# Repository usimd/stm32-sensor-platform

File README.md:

# stm32-sensor-platform
Extensible BLE/OpenThread sensor module based on STM32 for integration with HomeAssistant

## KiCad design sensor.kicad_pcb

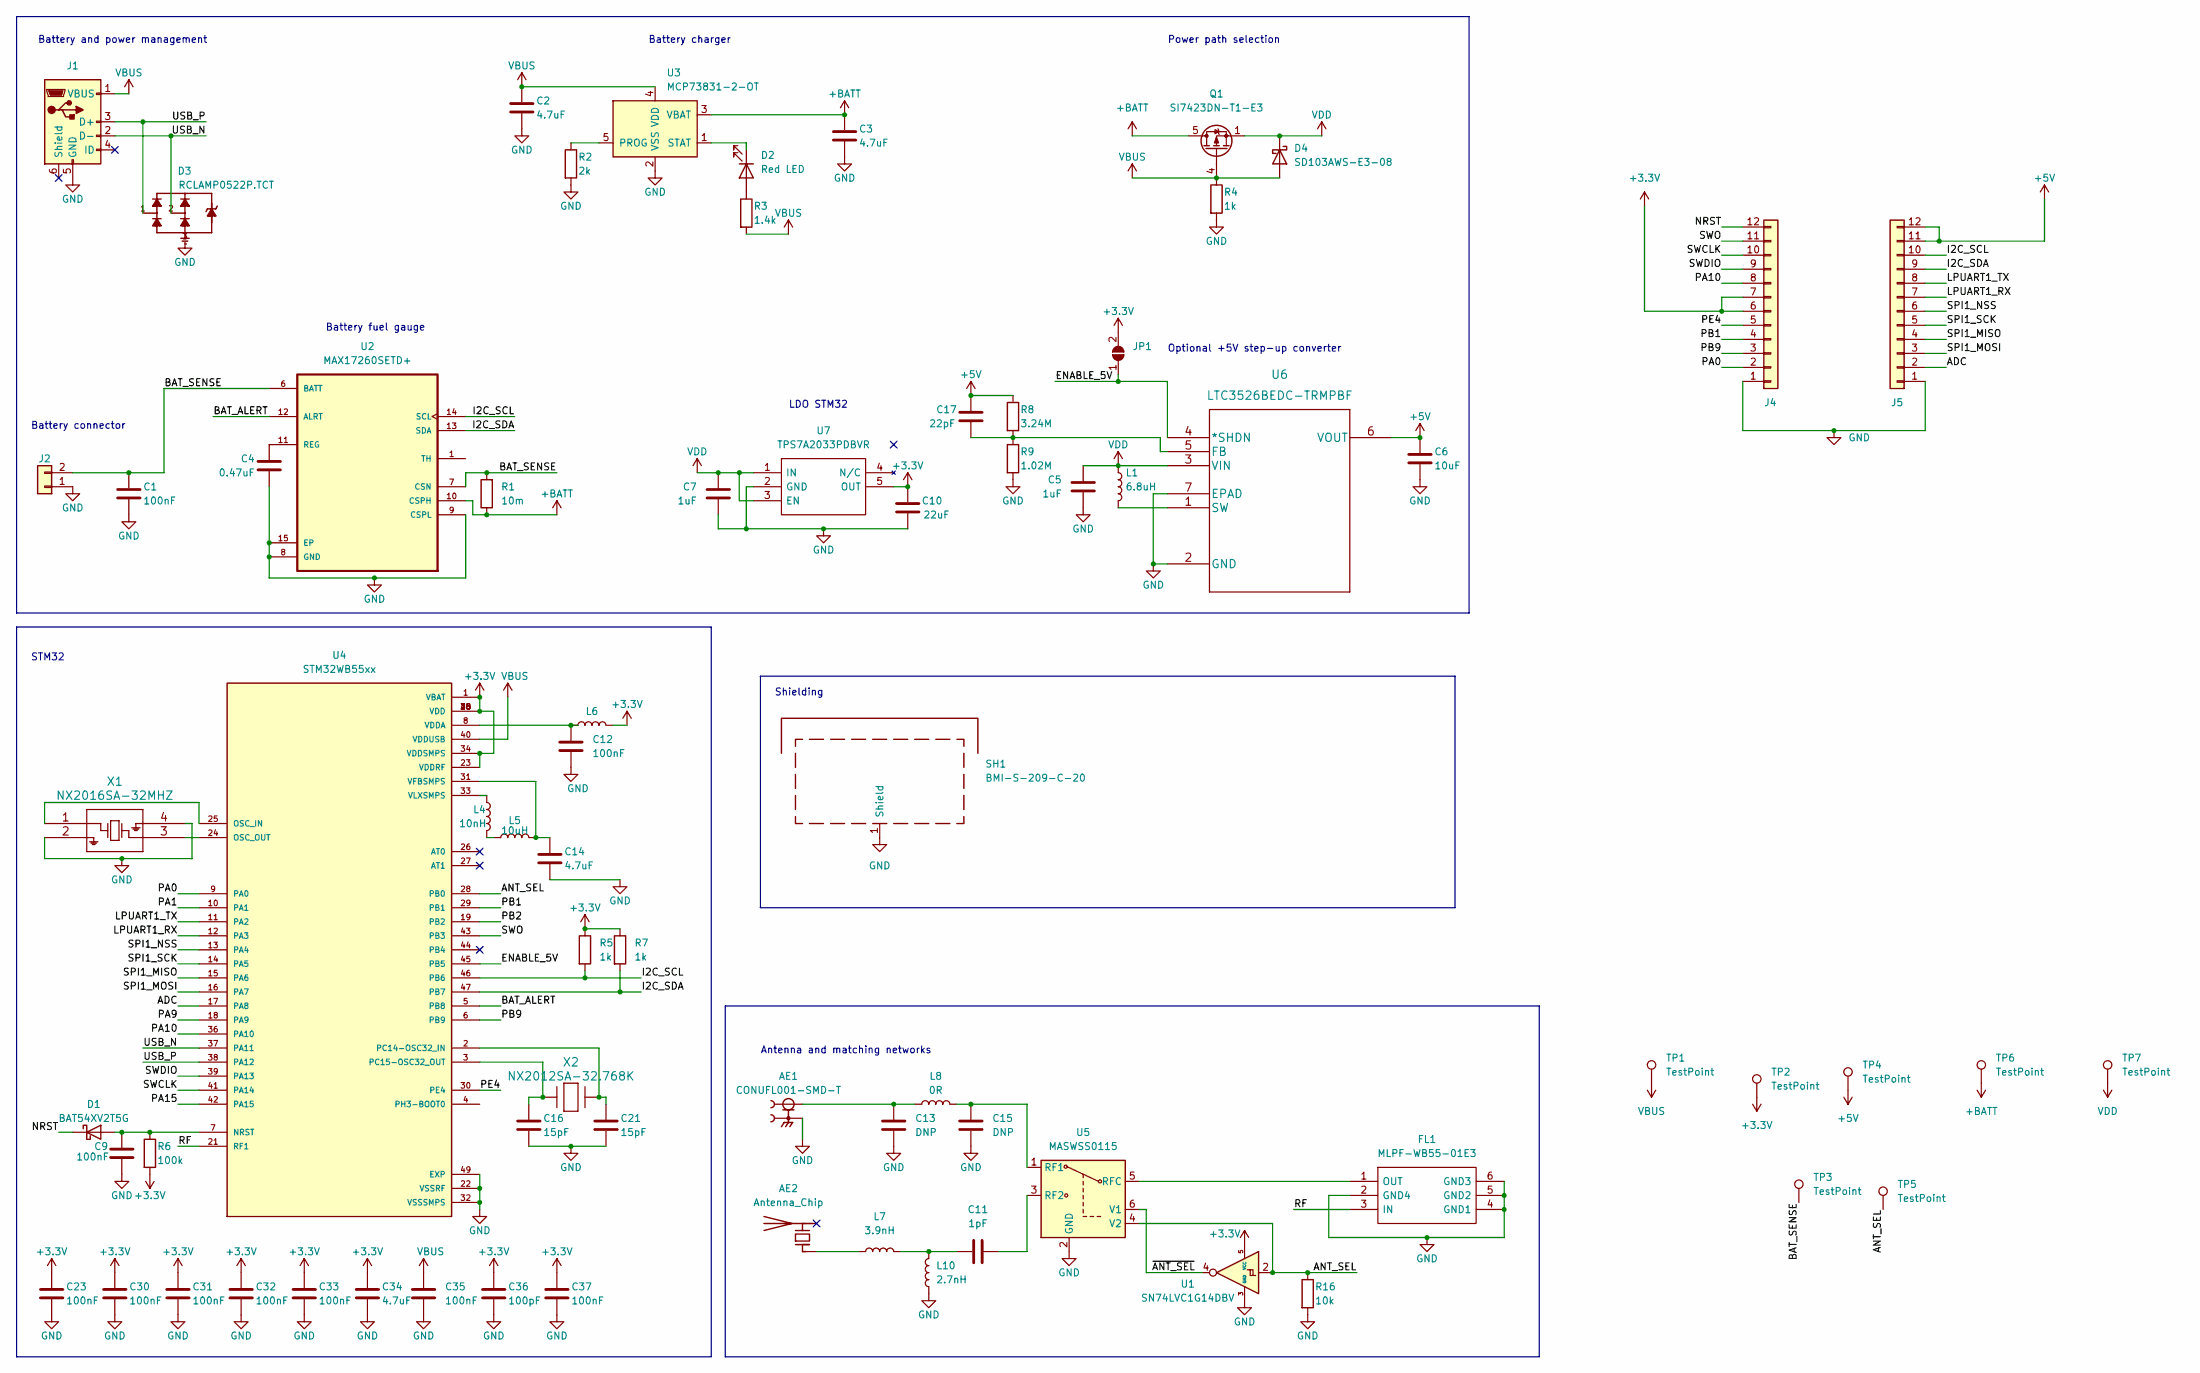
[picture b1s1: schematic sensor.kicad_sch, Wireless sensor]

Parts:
AE1: CONUFL001-SMD-T; LINX_CONUFL001-SMD-T; PARTREV B
AE2: Antenna_Chip; Johanson_2450AT18x100; MPN 2450AT18A100E
C1: 100nF; C_0402_1005Metric; MPN GRM155R62A104KE14J
C2, C3, C14, C34: 4.7uF; C_0402_1005Metric; MPN GRM155R61A475MEAAD
C4: 0.47uF; C_0603_1608Metric; MPN LMK063BBJ474KPLF
C5, C7: 1uF; C_0402_1005Metric; MPN CL05A105KP5NNNC
C6: 10uF; C_0603_1608Metric; MPN 0603ZD106KAT2A
C9, C12, C23, C30, C31, C32, C33, C35, C37: 100nF; C_0402_1005Metric; MPN GRM155R61H104KE19D
C10: 22uF; C_0603_1608Metric; MPN CL10A226KQ8NRNE
C11: 1pF; C_0402_1005Metric; MPN 500R07S1R0BV4T
C13, C15: DNP; C_0402_1005Metric
C16, C21: 15pF; C_0402_1005Metric; MPN GRM1555C1H4R3CA01D
C17: 22pF; C_0402_1005Metric; MPN C0402C220K4RACTU
C36: 100pF; C_0402_1005Metric; MPN CC0402KRX7R9BB101
D1: BAT54XV2T5G; D_SOD-523; MPN BAT54XV2T5G
D2: Red LED; LED_0603_1608Metric; MPN LS L29K-G1J2-1
D3: RCLAMP0522P.TCT; TVS_RCLAMP0522P.TCT; MPN RCLAMP0522P.TCT
D4: SD103AWS-E3-08; D_SOD-323; MPN SD103AWS-E3-08
FL1: MLPF-WB55-01E3; MLPFWB5501E3; Manufacturer_Part_Number MLPF-WB55-01E3; Mouser Part Number 511-MLPF-WB55-01E3
J1: 10103594-0001LF; USB_Micro-B_Amphenol_10103594-0001LF_Horizontal; MPN 10103594-0001LF
J2: Molex_PicoBlade_53261-0271_1x02-1MP_P1.25mm_Horizontal; MPN 53261-7002
J4, J5: Castellation_1x12_Drill
JP1: SolderJumper-2_P1.3mm_Open_TrianglePad1.0x1.5mm
L1: 6.8uH; L_Coilcraft_LPS4018; MPN LPS4018-682MRC
L4: 10nH; L_0402_1005Metric; MPN LQG15WZ10NJ02D
L5: 10uH; L_0805_2012Metric; MPN LQM21FN100M70L
L6: L_0603_1608Metric; MPN MMZ1608S601ATA00
L7: 3.9nH; L_0402_1005Metric; MPN L-07C3N9SV6T
L8: 0R; L_0402_1005Metric; MPN RC0402JR-100RL
L10: 2.7nH; L_0402_1005Metric; MPN L-07C2N7SV6T
Q1: SI7423DN-T1-E3; Vishay_PowerPAK_1212-8_Single; MPN SI7423DN-T1-E3
R1: 10m; R_0805_2012Metric; MPN ERJ-6CWDR010V
R2: 2k; R_0402_1005Metric; MPN ERJ-2RHD2001X
R3: 1.4k; R_0402_1005Metric; MPN ERJ-2RHD1401X
R4, R5, R7: 1k; R_0402_1005Metric; MPN RGC1/16SC1001DTH
R6: 100k; R_0402_1005Metric; MPN RC0402FR-10100KL
R8: 3.24M; R_0805_2012Metric; MPN RS73F2ATTD3244D
R9: 1.02M; R_0402_1005Metric; MPN CRCW04021M02FKED
R16: 10k; R_0402_1005Metric; MPN CRCW040210K0FKEDC
SH1: BMI-S-209-C-20; Laird_Technologies_BMI-S-209-F_29.36x18.50mm; MPN BMI-S-209-C-20
TP1, TP2, TP3, TP4, TP5, TP6, TP7: TestPoint; TestPoint_Pad_D1.0mm
U1: SN74LVC1G14DBV; SOT-23-5; MPN SN74LVC1G14DBV
U2: MAX17260SETD+; SON40P300X300X80-15N; MPN MAX17260SETD+
U3: MCP73831-2-OT; SOT-23-5; MPN MCP73831T-2ACI/OT
U4: STM32WB55xx; QFN50P700X700X60-49N; PARTREV 5
U5: MASWSS0115; SOT-363_SC-70-6; MPN MASWSS0115TR-3000
U6: LTC3526BEDC-TRMPBF; MPN LTC3526BEDC-TRMPBF
U7: TPS7A2033PDBVR; SOT95P280X145-5N; Manufacturer_Part_Number TPS7A2033PDBVR; Mouser Part Number 595-TPS7A2033PDBVR
X1: NX2016SA-32MHZ; NX2016SA-32MHZ-EXS00A-CS11213; MPN NX2016SA-32M-EXS00A-CS06465
X2: NX2012SA-32.768K; NX2012SA-32.768K-STD-MUB-1; MPN NX2012SA-32.768K-STD-MUB-1

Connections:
+3.3V: C10.1, C23.1, C30.1, C31.1, C32.1, C33.1, C34.1, C36.1, C37.1, J4.6, J4.7, JP1.2 (B), L6.2, R5.1, R6.2, R7.1, TP2.1, U1.5 (VCC), U4.1 (VBAT), U4.20 (VDD), U4.23 (VDDRF), U4.34 (VDDSMPS), U4.35 (VDD), U4.48 (VDD), U7.5 (OUT)
+5V: C6.1, C17.1, J5.11, J5.12, R8.1, TP4.1, U6.6 (VOUT)
+BATT: C3.1, Q1.5 (D), R1.1, TP6.1, U2.10 (CSPH), U3.3 (VBAT)
/ADC: J5.2, U4.17 (PA8)
/ANT_SEL: R16.1, TP5.1, U1.2, U4.28 (PB0), U5.4 (V2)
/BAT_ALERT: U2.12 (ALRT), U4.5 (PB8)
/BAT_SENSE: C1.1, J2.2, R1.2, TP3.1, U2.6 (BATT), U2.7 (CSN)
/ENABLE_5V: JP1.1 (A), U4.45 (PB5), U6.4 (*SHDN)
/I2C_SCL: J5.10, R5.2, U2.14 (SCL), U4.46 (PB6)
/I2C_SDA: J5.9, R7.2, U2.13 (SDA), U4.47 (PB7)
/LPUART1_RX: J5.7, U4.12 (PA3)
/LPUART1_TX: J5.8, U4.11 (PA2)
/NRST: D1.1 (K), J4.12
/PA0: J4.2, U4.9 (PA0)
/PA1: U4.10 (PA1)
/PA9: U4.18 (PA9)
/PA10: J4.8, U4.36 (PA10)
/PA15: U4.42 (PA15)
/PB1: J4.4, U4.29 (PB1)
/PB2: U4.19 (PB2)
/PB9: J4.3, U4.6 (PB9)
/PE4: J4.5, U4.30 (PE4)
/RF: FL1.3 (IN), U4.21 (RF1)
/SPI1_MISO: J5.4, U4.15 (PA6)
/SPI1_MOSI: J5.3, U4.16 (PA7)
/SPI1_NSS: J5.6, U4.13 (PA4)
/SPI1_SCK: J5.5, U4.14 (PA5)
/SWCLK: J4.10, U4.41 (PA14)
/SWDIO: J4.9, U4.39 (PA13)
/SWO: J4.11, U4.43 (PB3)
/USB_N: D3.2, J1.2 (D-), U4.37 (PA11)
/USB_P: D3.1, J1.3 (D+), U4.38 (PA12)
/~ANT_SEL: U1.4, U5.6 (V1)
GND: AE1.2, AE1.3, C1.2, C2.2, C3.2, C4.2, C5.1, C6.2, C7.1, C9.2, C10.2, C12.2, C13.2, C14.2, C15.2, C16.2, C21.2, C23.2, C30.2, C31.2, C32.2, C33.2, C34.2, C35.2, C36.2, C37.2, D3.3, FL1.2 (GND4), FL1.4 (GND1), FL1.5 (GND2), FL1.6 (GND3), J1.5 (GND), J2.1, J4.1, J5.1, L10.1, R2.2, R4.2, R9.2, R16.2, SH1.1 (Shield), U1.3 (GND), U2.8 (GND), U2.9 (CSPL), U2.15 (EP), U3.2 (VSS), U4.22 (VSSRF), U4.32 (VSSSMPS), U4.49 (EXP), U5.2 (GND), U6.2 (GND), U6.7 (EPAD), U7.2 (GND), X1.2, X1.4
unnamed: AE1.1, C13.1, L8.1
unnamed: AE2.1 (FEED), L7.1
unnamed: C4.1, U2.11 (REG)
unnamed: C9.1, D1.2 (A), R6.1, U4.7 (NRST)
unnamed: C11.1, L7.2, L10.2
unnamed: C11.2, U5.3 (RF2)
unnamed: C12.1, L6.1, U4.8 (VDDA)
unnamed: C14.1, L5.2, U4.31 (VFBSMPS)
unnamed: C15.1, L8.2, U5.1 (RF1)
unnamed: C16.1, U4.3 (PC15-OSC32_OUT), X2.2
unnamed: C17.2, R8.2, R9.1, U6.5 (FB)
unnamed: C21.1, U4.2 (PC14-OSC32_IN), X2.1
unnamed: D2.1 (K), U3.1 (STAT)
unnamed: D2.2 (A), R3.1
unnamed: FL1.1 (OUT), U5.5 (RFC)
unnamed: L1.2, U6.1 (SW)
unnamed: L4.1, U4.33 (VLXSMPS)
unnamed: L4.2, L5.1
unnamed: R2.1, U3.5 (PROG)
unnamed: U4.24 (OSC_OUT), X1.3
unnamed: U4.25 (OSC_IN), X1.1
VBUS: C2.1, C35.1, D4.2 (A), J1.1 (VBUS), Q1.4 (G), R3.2, R4.1, TP1.1, U3.4 (VDD), U4.40 (VDDUSB)
VDD: C5.2, C7.2, D4.1 (K), L1.1, Q1.1 (S), Q1.2 (S), Q1.3 (S), TP7.1, U6.3 (VIN), U7.1 (IN), U7.3 (EN)

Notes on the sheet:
STM32
Power path selection
LDO STM32
Shielding
Battery charger
Battery connector
Battery and power management
Battery fuel gauge
Optional +5V step-up converter
Antenna and matching networks

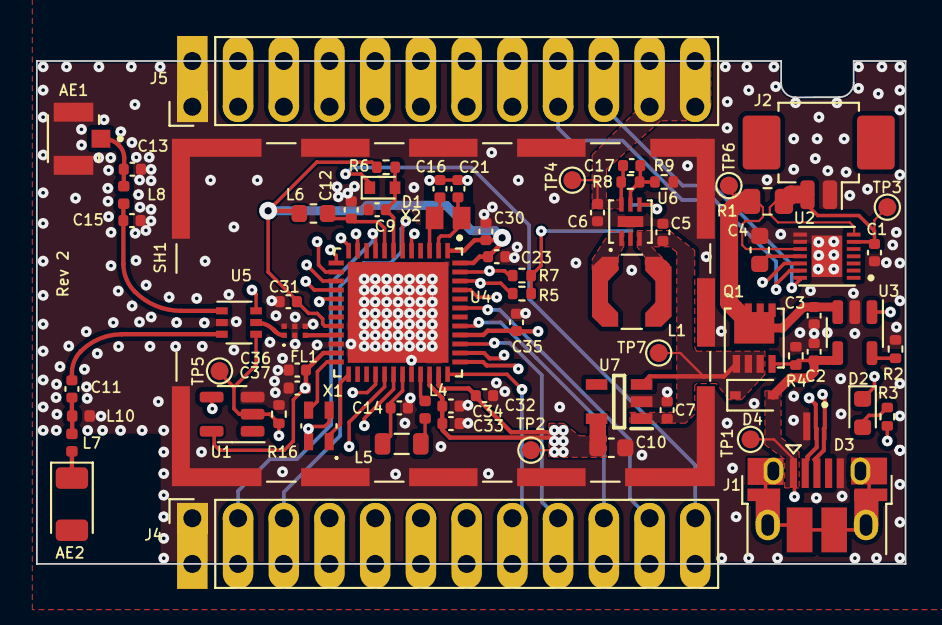
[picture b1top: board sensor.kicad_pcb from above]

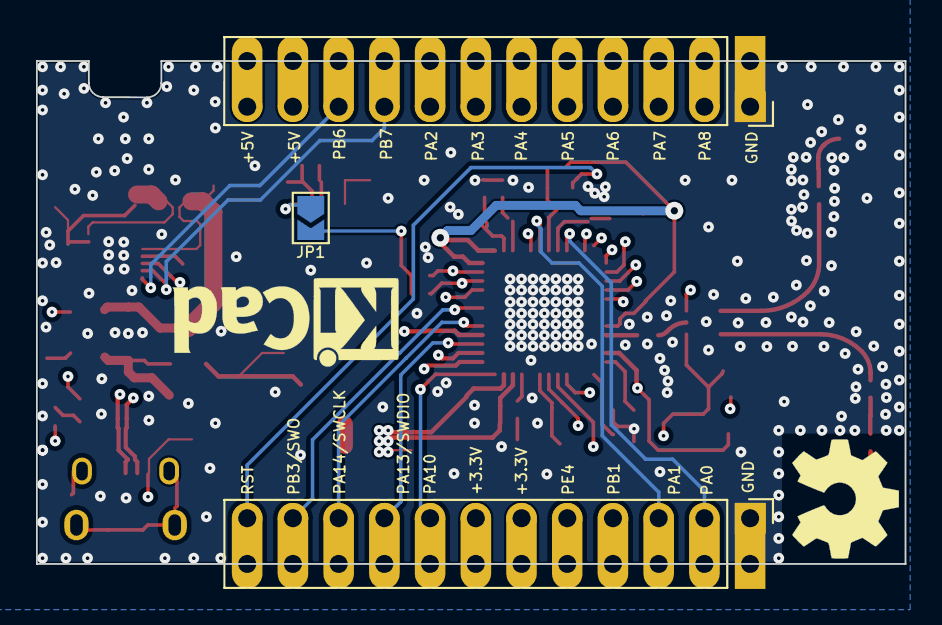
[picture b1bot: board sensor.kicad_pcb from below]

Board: 4 copper layers, 48.3 x 27.9 mm, 73 parts (2 on the bottom side), 53 nets.

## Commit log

2022-09-30 Initial import
2022-10-02 First full draft
2022-10-17 Added I2C ports, rev2

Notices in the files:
parts and their libraries:
Copyright 2021 Accelerated Designs. All rights reserved.
